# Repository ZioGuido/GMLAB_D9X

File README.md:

# GMLAB_D9X
Repository for the GMLAB D9X Midi Drawbar Controller

This repository contains the full sources of the GMLAB D9X Midi Drawbar Controller.
Please refer to the included PDF document for details about the project.

Project home page:
http://www.gmlab.it/

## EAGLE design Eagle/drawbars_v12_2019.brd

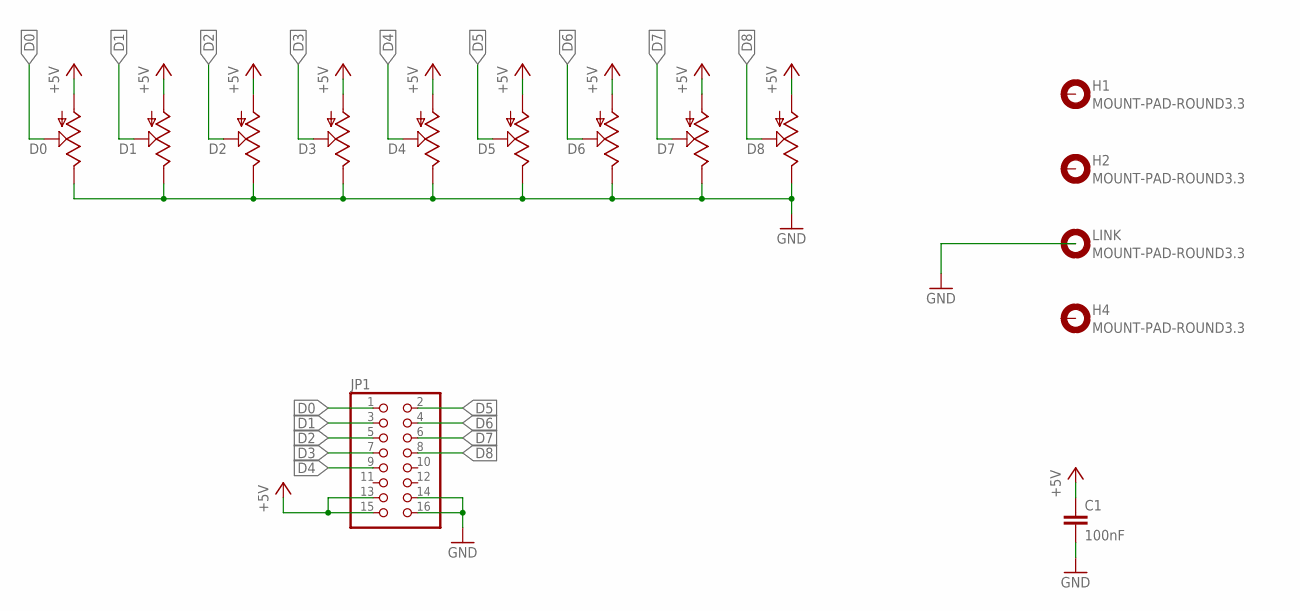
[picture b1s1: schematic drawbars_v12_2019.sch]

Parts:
C1: 100nF; C050-024X044
D0, D1, D2, D3, D4, D5, D6, D7, D8: POTENTIOMETER; ALPHA_DRAWBARS
H1, H2, H4: MOUNT-PAD-ROUND3.3; 3,3-PAD
JP1: PINHD-2X8; 2X08
LINK: MOUNT-PAD-ROUND3.3; 3,3-PAD

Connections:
+5V: C1.1, D0.P$2 (1), D1.P$2 (1), D2.P$2 (1), D3.P$2 (1), D4.P$2 (1), D5.P$2 (1), D6.P$2 (1), D7.P$2 (1), D8.P$2 (1), JP1.13, JP1.15
D0: D0.P$3 (2), JP1.1
D1: D1.P$3 (2), JP1.3
D2: D2.P$3 (2), JP1.5
D3: D3.P$3 (2), JP1.7
D4: D4.P$3 (2), JP1.9
D5: D5.P$3 (2), JP1.2
D6: D6.P$3 (2), JP1.4
D7: D7.P$3 (2), JP1.6
D8: D8.P$3 (2), JP1.8
GND: C1.2, D0.P$1 (3), D1.P$1 (3), D2.P$1 (3), D3.P$1 (3), D4.P$1 (3), D5.P$1 (3), D6.P$1 (3), D7.P$1 (3), D8.P$1 (3), JP1.14, JP1.16

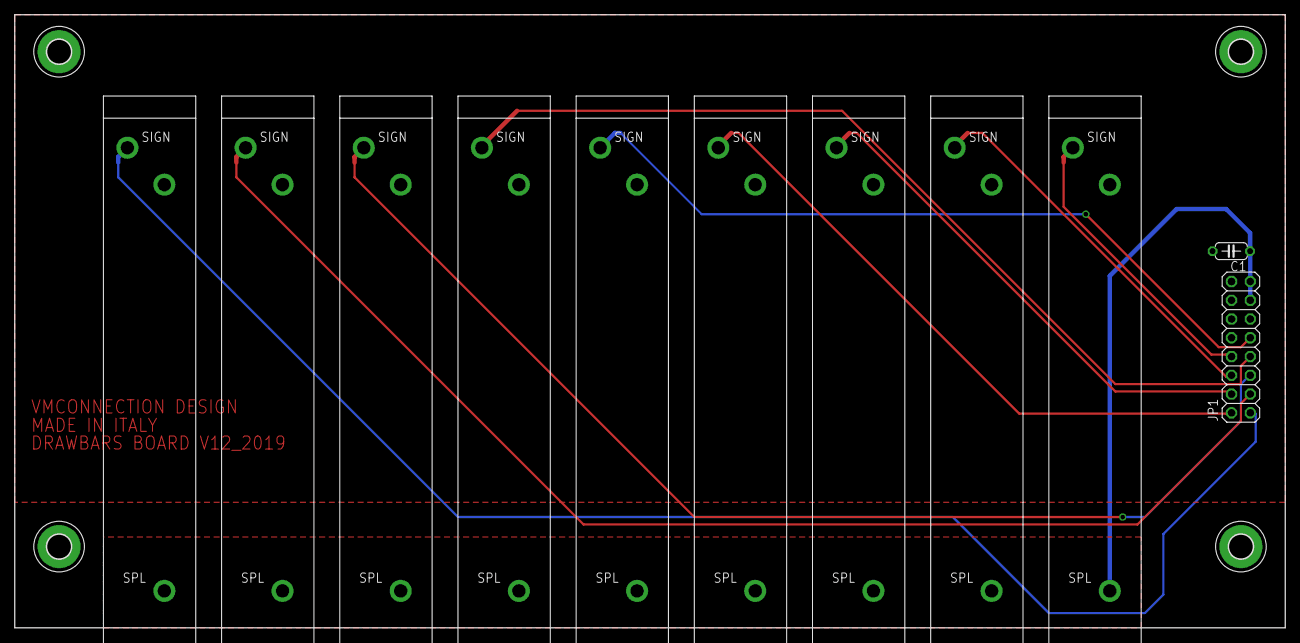
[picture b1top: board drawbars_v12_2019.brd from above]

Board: 2 copper layers, 172.0 x 83.0 mm, 15 parts (0 on the bottom side), 11 nets.

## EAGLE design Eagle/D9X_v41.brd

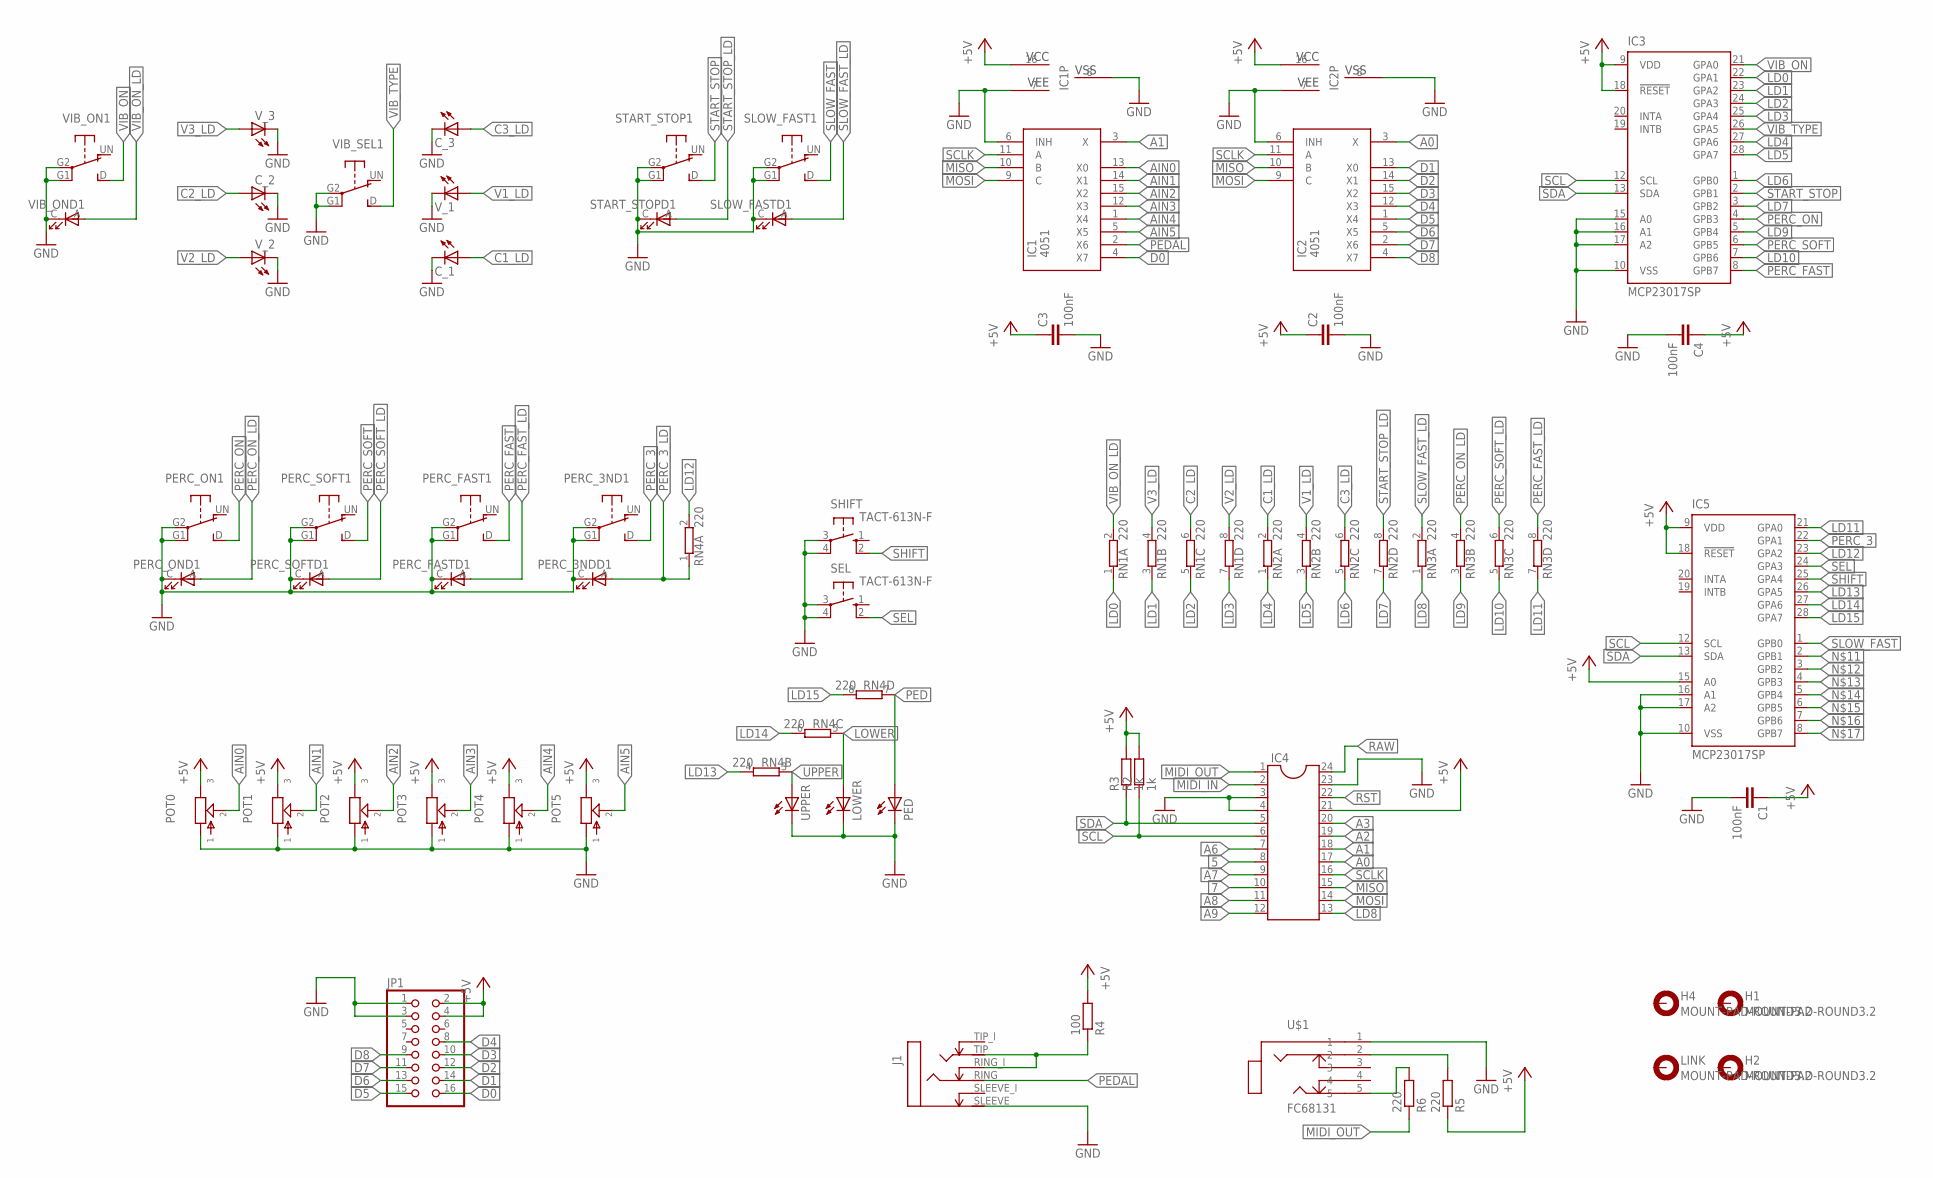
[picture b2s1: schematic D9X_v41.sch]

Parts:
C1, C2, C3, C4: 100nF; C050-024X044
C_1, C_2, C_3: LED3MM
H1, H2, H4: MOUNT-PAD-ROUND3.2; 3,2-PAD
IC1, IC2: 4051; DIL16
IC3, IC5: MCP23017SP; DIL28-3
IC4: DIL24-6
J1: STEREOSWJACK_ST_TRS_INT; ST_JACK_TRS_INT
JP1: PINHD-2X8; 2X08
LINK: MOUNT-PAD-ROUND3.2; 3,2-PAD
LOWER: LED3MM
PED: LED3MM
PERC_3ND: SRKLSHANPU; SP86N-A1-5-01
PERC_FAST: SRKLSHANPU; SP86N-A1-5-01
PERC_ON: SRKLSHANPU; SP86N-A1-5-01
PERC_SOFT: SRKLSHANPU; SP86N-A1-5-01
POT0, POT1, POT2, POT3, POT4, POT5: POT-EU12MM; RV120DF-40B1-(L)K
R2, R3: 1k; 0204/7
R4: 100; 0204/7
R5, R6: 220; 0204/7
RN1, RN2, RN3, RN4: 220; SIL8
SEL: TACT-613N-F; B3F-10XX
SHIFT: TACT-613N-F; B3F-10XX
SLOW_FAST: SRKLSHANPU; SP86N-A1-5-01
START_STOP: SRKLSHANPU; SP86N-A1-5-01
U$1: FC68131; FC68131-5P
UPPER: LED3MM
VIB_ON: SRKLSHANPU; SP86N-A1-5-01
VIB_SEL: SRKLSHANPU; SP86N-A1-5-01
V_1, V_2, V_3: LED3MM

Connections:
5: IC4.8
7: IC4.10
+5V: C1.1, C2.1, C3.1, C4.1, IC1.16 (VCC), IC2.16 (VCC), IC3.9 (VDD), IC3.18 (!RESET), IC4.21, IC5.9 (VDD), IC5.15 (A0), IC5.18 (!RESET), JP1.2, JP1.4, POT0.3, POT1.3, POT2.3, POT3.3, POT4.3, POT5.3, R2.2, R3.2, R4.2, R5.1
A0: IC2.3 (X), IC4.17
A1: IC1.3 (X), IC4.18
A2: IC4.19
A3: IC4.20
A6: IC4.7
A7: IC4.9
A8: IC4.11
A9: IC4.12
AIN0: IC1.13 (X0), POT0.2
AIN1: IC1.14 (X1), POT1.2
AIN2: IC1.15 (X2), POT2.2
AIN3: IC1.12 (X3), POT3.2
AIN4: IC1.1 (X4), POT4.2
AIN5: IC1.5 (X5), POT5.2
C1_LD: C_1.A, RN2.2
C2_LD: C_2.A, RN1.6 (2)
C3_LD: C_3.A, RN2.6 (2)
D0: IC1.4 (X7), JP1.16
D1: IC2.13 (X0), JP1.14
D2: IC2.14 (X1), JP1.12
D3: IC2.15 (X2), JP1.10
D4: IC2.12 (X3), JP1.8
D5: IC2.1 (X4), JP1.15
D6: IC2.5 (X5), JP1.13
D7: IC2.2 (X6), JP1.11
D8: IC2.4 (X7), JP1.9
GND: C1.2, C2.2, C3.2, C4.2, C_1.K (C), C_2.K (C), C_3.K (C), IC1.6 (INH), IC1.7 (VEE), IC1.8 (VSS), IC2.6 (INH), IC2.7 (VEE), IC2.8 (VSS), IC3.10 (VSS), IC3.15 (A0), IC3.16 (A1), IC3.17 (A2), IC4.3, IC4.4, IC4.23, IC5.10 (VSS), IC5.16 (A1), IC5.17 (A2), J1.SLEEVE (S), JP1.1, JP1.3, LOWER.K (C), PED.K (C), PERC_3ND.C, PERC_3ND.G1, PERC_3ND.G2, PERC_FAST.C, PERC_FAST.G1, PERC_FAST.G2, PERC_ON.C, PERC_ON.G1, PERC_ON.G2, PERC_SOFT.C, PERC_SOFT.G1, PERC_SOFT.G2, POT0.1, POT1.1, POT2.1, POT3.1, POT4.1, POT5.1, SEL.3, SEL.4 (P1), SHIFT.3, SHIFT.4 (P1), SLOW_FAST.C, SLOW_FAST.G1, SLOW_FAST.G2, START_STOP.C, START_STOP.G1, START_STOP.G2, U$1.1, UPPER.K (C), VIB_ON.C, VIB_ON.G1, VIB_ON.G2, VIB_SEL.G1, VIB_SEL.G2, V_1.K (C), V_2.K (C), V_3.K (C)
LD0: IC3.22 (GPA1), RN1.1
LD1: IC3.23 (GPA2), RN1.3 (1)
LD2: IC3.24 (GPA3), RN1.5 (1)
LD3: IC3.25 (GPA4), RN1.7 (1)
LD4: IC3.27 (GPA6), RN2.1
LD5: IC3.28 (GPA7), RN2.3 (1)
LD6: IC3.1 (GPB0), RN2.5 (1)
LD7: IC3.3 (GPB2), RN2.7 (1)
LD8: IC4.13, RN3.1
LD9: IC3.5 (GPB4), RN3.3 (1)
LD10: IC3.7 (GPB6), RN3.5 (1)
LD11: IC5.21 (GPA0), RN3.7 (1)
LD12: IC5.23 (GPA2), RN4.2
LD13: IC5.26 (GPA5), RN4.4 (2)
LD14: IC5.27 (GPA6), RN4.6 (2)
LD15: IC5.28 (GPA7), RN4.8 (2)
LOWER: LOWER.A, RN4.5 (1)
MIDI_IN: IC4.2
MIDI_OUT: IC4.1, R6.1
MISO: IC1.10 (B), IC2.10 (B), IC4.15
MOSI: IC1.9 (C), IC2.9 (C), IC4.14
unnamed: J1.RING_I (RN), J1.TIP (T), R4.1
unnamed: R5.2, U$1.2
unnamed: R6.2, U$1.5
PED: PED.A, RN4.7 (1)
PEDAL: IC1.2 (X6), J1.RING (R)
PERC_3: IC5.22 (GPA1), PERC_3ND.D (S)
PERC_3_LD: PERC_3ND.A, RN4.1
PERC_FAST: IC3.8 (GPB7), PERC_FAST.D (S)
PERC_FAST_LD: PERC_FAST.A, RN3.8 (2)
PERC_ON: IC3.4 (GPB3), PERC_ON.D (S)
PERC_ON_LD: PERC_ON.A, RN3.4 (2)
PERC_SOFT: IC3.6 (GPB5), PERC_SOFT.D (S)
PERC_SOFT_LD: PERC_SOFT.A, RN3.6 (2)
RAW: IC4.24
RST: IC4.22
SCL: IC3.12 (SCL), IC4.6, IC5.12 (SCL), R2.1
SCLK: IC1.11 (A), IC2.11 (A), IC4.16
SDA: IC3.13 (SDA), IC4.5, IC5.13 (SDA), R3.1
SEL: IC5.24 (GPA3), SEL.2 (S1)
SHIFT: IC5.25 (GPA4), SHIFT.2 (S1)
SLOW_FAST: IC5.1 (GPB0), SLOW_FAST.D (S)
SLOW_FAST_LD: RN3.2, SLOW_FAST.A
START_STOP: IC3.2 (GPB1), START_STOP.D (S)
START_STOP_LD: RN2.8 (2), START_STOP.A
UPPER: RN4.3 (1), UPPER.A
V1_LD: RN2.4 (2), V_1.A
V2_LD: RN1.8 (2), V_2.A
V3_LD: RN1.4 (2), V_3.A
VIB_ON: IC3.21 (GPA0), VIB_ON.D (S)
VIB_ON_LD: RN1.2, VIB_ON.A
VIB_TYPE: IC3.26 (GPA5), VIB_SEL.D (S)

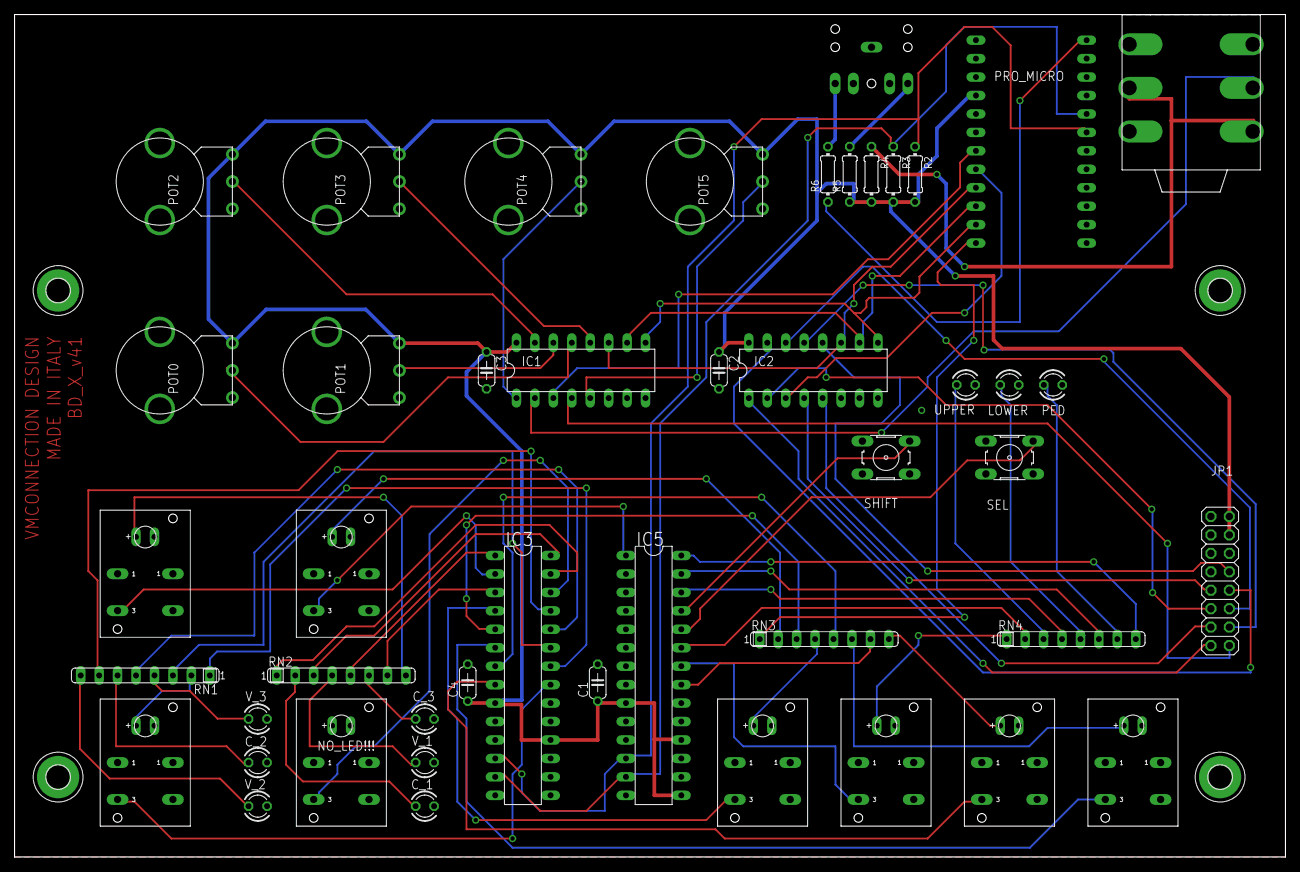
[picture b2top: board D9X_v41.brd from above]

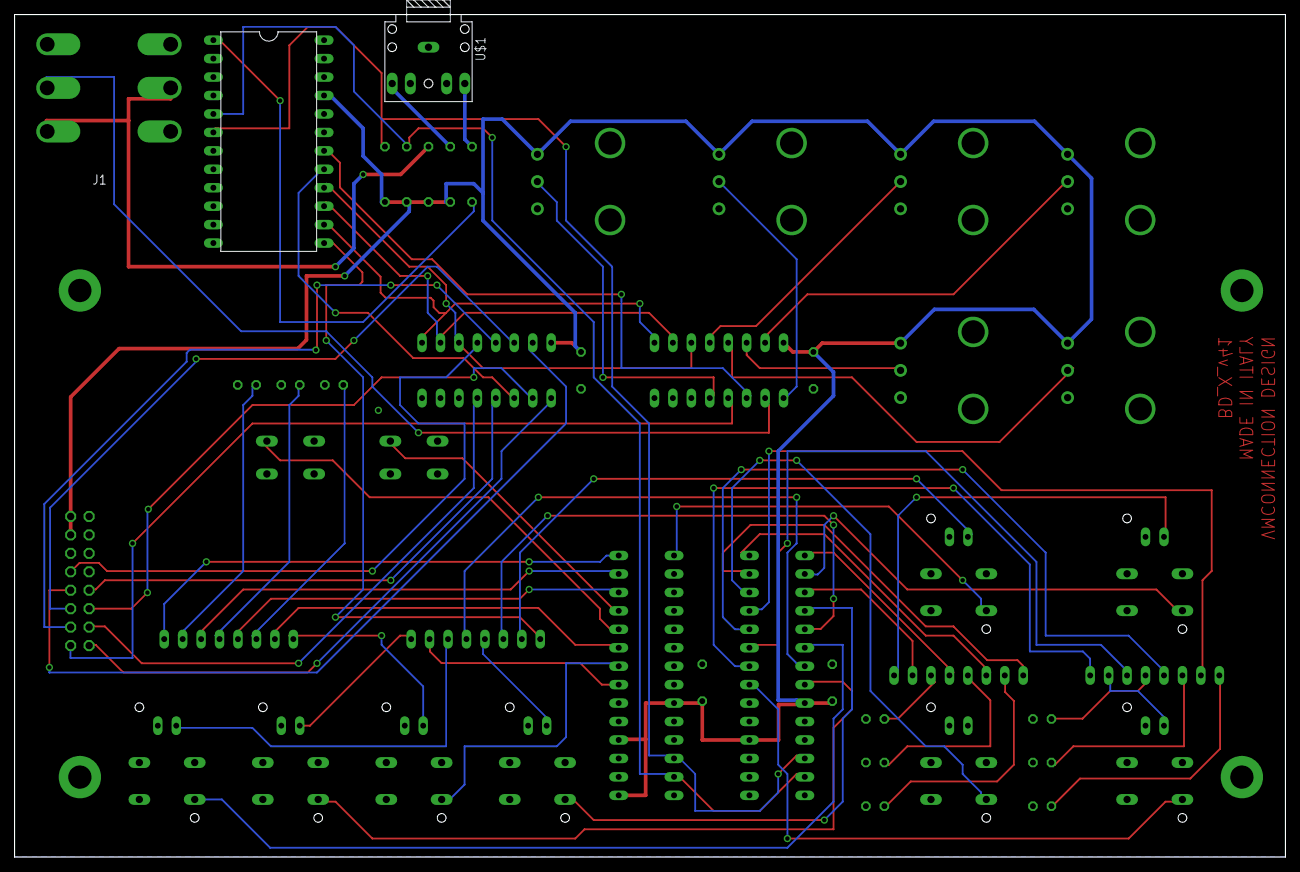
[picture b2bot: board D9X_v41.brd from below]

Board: 2 copper layers, 175.0 x 116.0 mm, 50 parts (3 on the bottom side), 71 nets.

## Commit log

2023-04-02 send brake release if rotary speed changed while locked
2023-04-02 Updated to work with Adafruit_MCP23x17 library v2.3.0
2023-04-05 Better ErrorState blink mechanism

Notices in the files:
parts and their libraries:
atari: Copyright (c) 2010
Copyright (c) 2009
This library is licensed under the
Creative Commons Attribution 3.0 United States License.
